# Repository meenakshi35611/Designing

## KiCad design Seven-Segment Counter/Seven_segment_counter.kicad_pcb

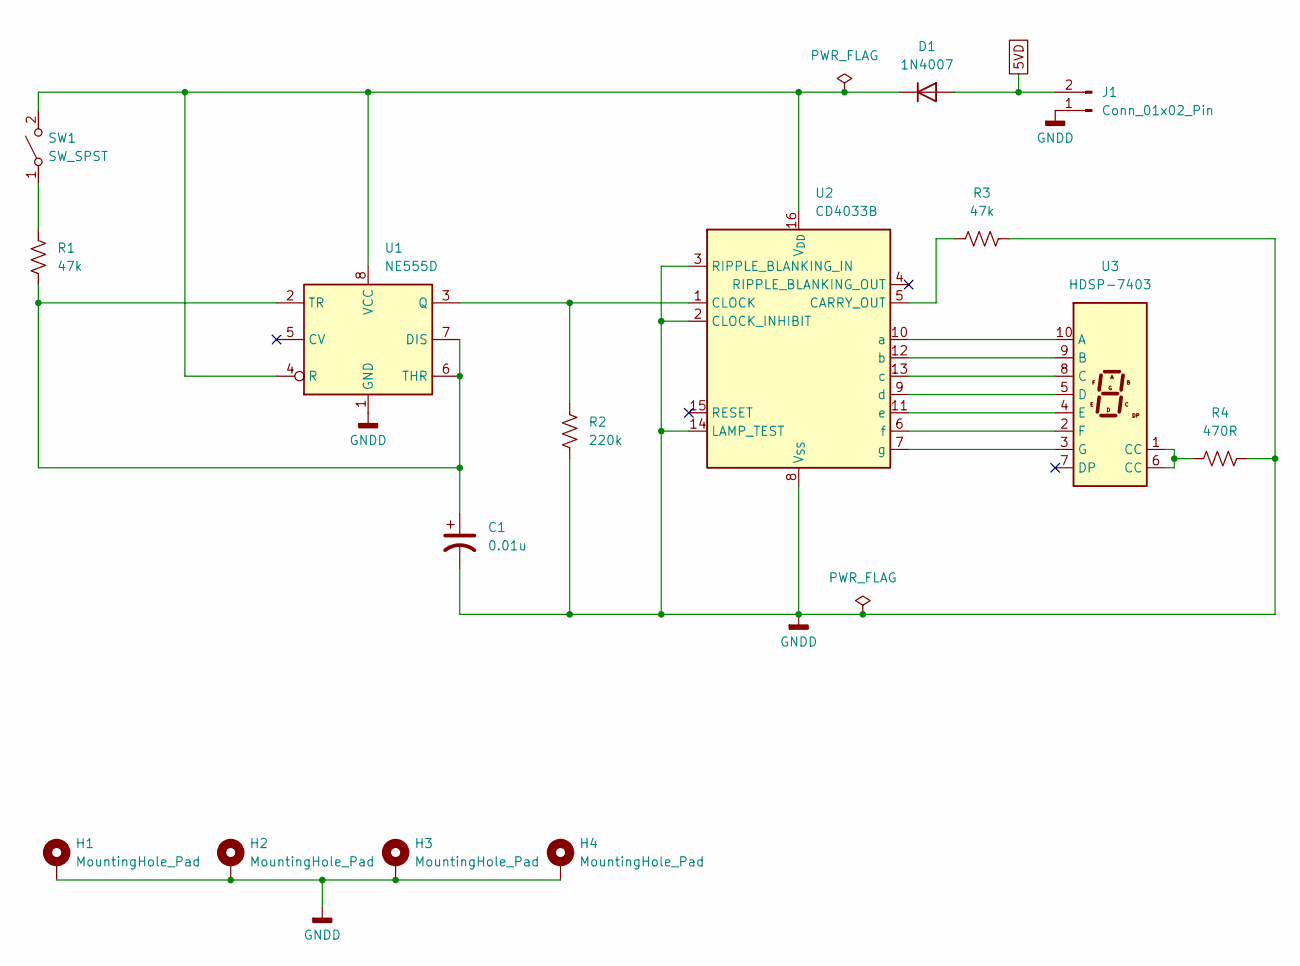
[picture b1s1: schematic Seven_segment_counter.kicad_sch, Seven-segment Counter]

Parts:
C1: 0.01u; C_0805_2012Metric
D1: 1N4007; D_DO-41_SOD81_P10.16mm_Horizontal
H1, H2, H3, H4: MountingHole_Pad; MountingHole_3.2mm_M3_Pad
J1: Conn_01x02_Pin; PinHeader_1x02_P2.54mm_Vertical
R1, R3: 47k; R_0805_2012Metric
R2: 220k; R_0805_2012Metric
R4: 470R; R_1206_3216Metric
SW1: SW_SPST; SW_DIP_SPSTx01_Slide_9.78x4.72mm_W7.62mm_P2.54mm
U1: NE555D; SOIC-8_3.9x4.9mm_P1.27mm
U2: CD4033B; DIP-16_W7.62mm
U3: HDSP-7403; HDSP-7401

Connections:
5VD: D1.2 (A), J1.2
GNDD: C1.2, H1.1, H2.1, H3.1, H4.1, J1.1, R2.2, R3.2, R4.1, U1.1 (GND), U2.2 (CLOCK_INHIBIT), U2.3 (RIPPLE_BLANKING_IN), U2.8 (V_{SS}), U2.14 (LAMP_TEST)
unnamed: D1.1 (K), SW1.2 (B), U1.4 (R), U1.8 (VCC), U2.16 (V_{DD})
unnamed: R4.2, U3.1 (CC), U3.6 (CC)
unnamed: R1.1, SW1.1 (A)
unnamed: C1.1, R1.2, U1.2 (TR), U1.6 (THR), U1.7 (DIS)
unnamed: R2.1, U1.3 (Q), U2.1 (CLOCK)
unnamed: R3.1, U2.5 (CARRY_OUT)
unnamed: U2.10 (a), U3.10 (A)
unnamed: U2.12 (b), U3.9 (B)
unnamed: U2.13 (c), U3.8 (C)
unnamed: U2.9 (d), U3.5 (D)
unnamed: U2.11 (e), U3.4 (E)
unnamed: U2.6 (f), U3.2 (F)
unnamed: U2.7 (g), U3.3 (G)

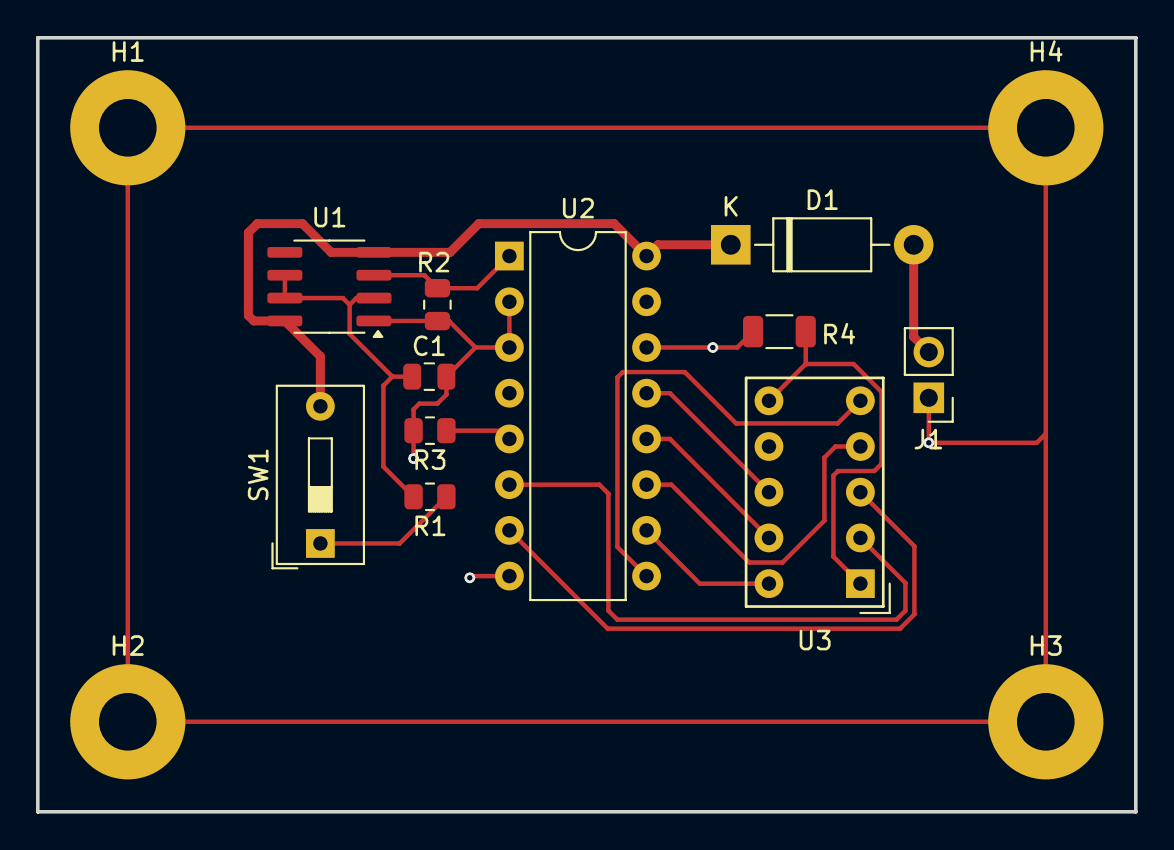
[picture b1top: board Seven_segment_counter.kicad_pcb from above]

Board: 2 copper layers, 61.0 x 43.0 mm, 15 parts (0 on the bottom side), 15 nets.

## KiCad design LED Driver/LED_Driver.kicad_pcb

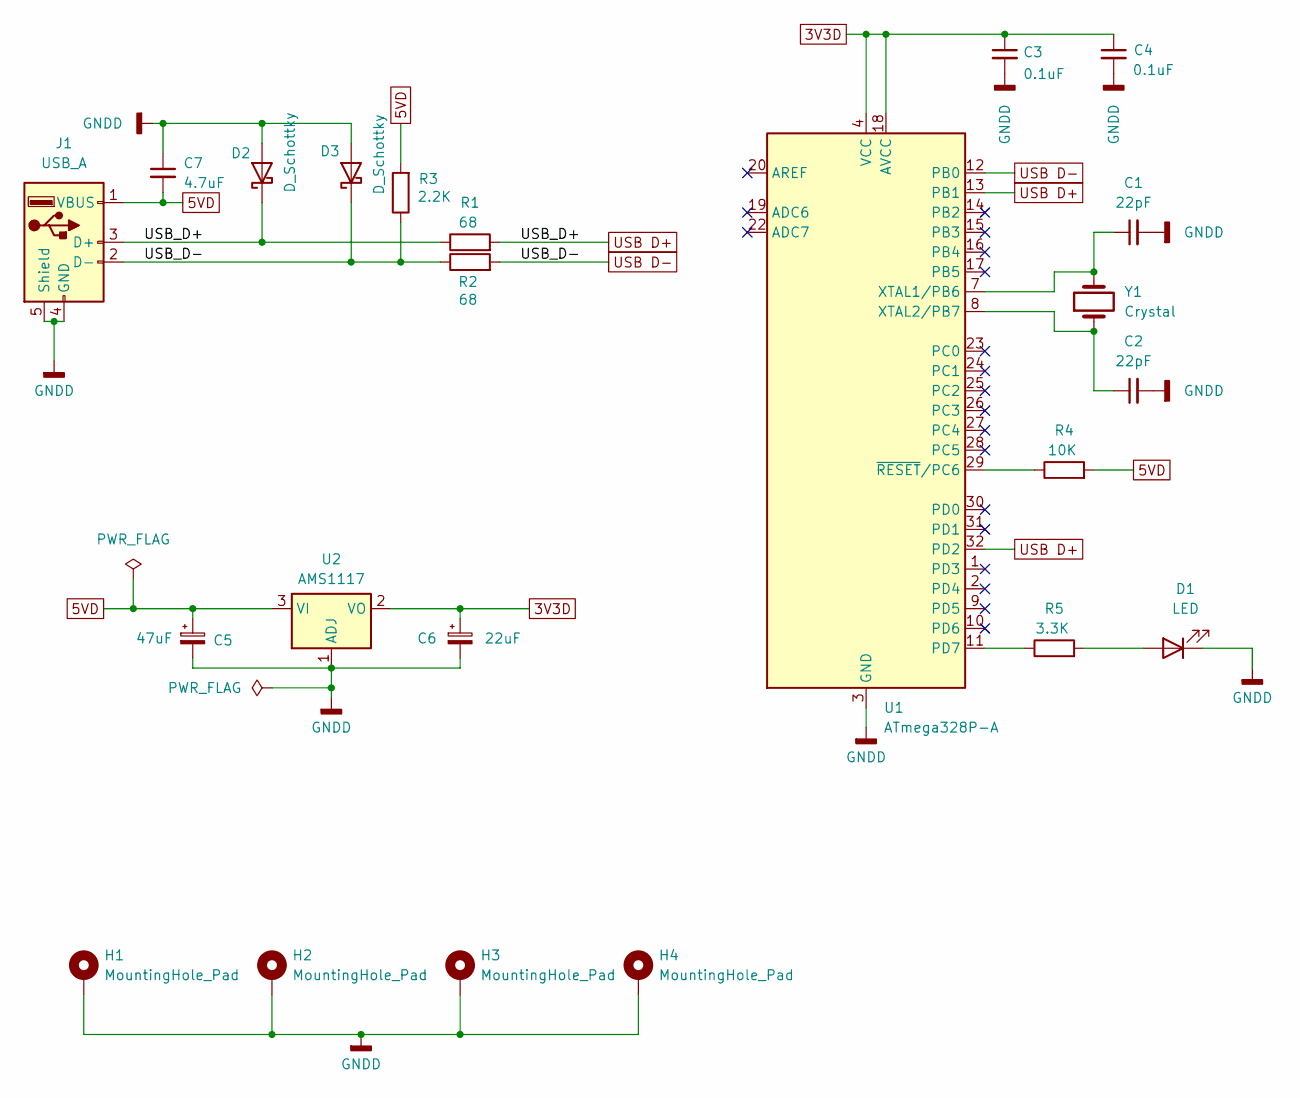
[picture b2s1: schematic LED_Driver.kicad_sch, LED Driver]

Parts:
C1, C2: 22pF; C_0805_2012Metric
C3, C4: 0.1uF; C_0805_2012Metric
C5: 47uF; C_1210_3225Metric
C6: 22uF; C_1210_3225Metric
C7: 4.7uF; C_1206_3216Metric
D1: LED; LED_D3.0mm
D2, D3: D_Schottky; D_SMA
H1, H2, H3, H4: MountingHole_Pad; MountingHole_3.2mm_M3_Pad
J1: USB_A; USB_A_Molex_67643_Horizontal
R1, R2: 68; R_0805_2012Metric
R3: 2.2K; R_0805_2012Metric
R4: 10K; R_0805_2012Metric
R5: 3.3K; R_0805_2012Metric
U1: ATmega328P-A; TQFP-32_7x7mm_P0.8mm
U2: AMS1117; SOT-223-3_TabPin2
Y1: Crystal; Crystal_SMD_HC49-SD

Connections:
3V3D: C3.1, C4.1, C6.1, U1.4 (VCC), U1.6 (VCC), U1.18 (AVCC), U2.2 (VO)
5VD: C5.1, C7.2, J1.1 (VBUS), R3.2, R4.2, U2.3 (VI)
GNDD: C1.2, C2.2, C3.2, C4.2, C5.2, C6.2, C7.1, D1.1 (K), D2.2 (A), D3.2 (A), H1.1, H2.1, H3.1, H4.1, J1.4 (GND), J1.5 (Shield), U1.3 (GND), U1.5 (GND), U1.21 (GND), U2.1 (ADJ)
unnamed: D1.2 (A), R5.2
unnamed: R5.1, U1.11 (PD7)
unnamed: C1.1, U1.7 (XTAL1/PB6), Y1.2
unnamed: C2.1, U1.8 (XTAL2/PB7), Y1.1
unnamed: R4.1, U1.29 (~RESET/PC6)
USB D+: D2.1 (K), J1.3 (D+), R1.1, R1.2, U1.13 (PB1), U1.32 (PD2)
USB D-: D3.1 (K), J1.2 (D-), R2.1, R2.2, R3.1, U1.12 (PB0)

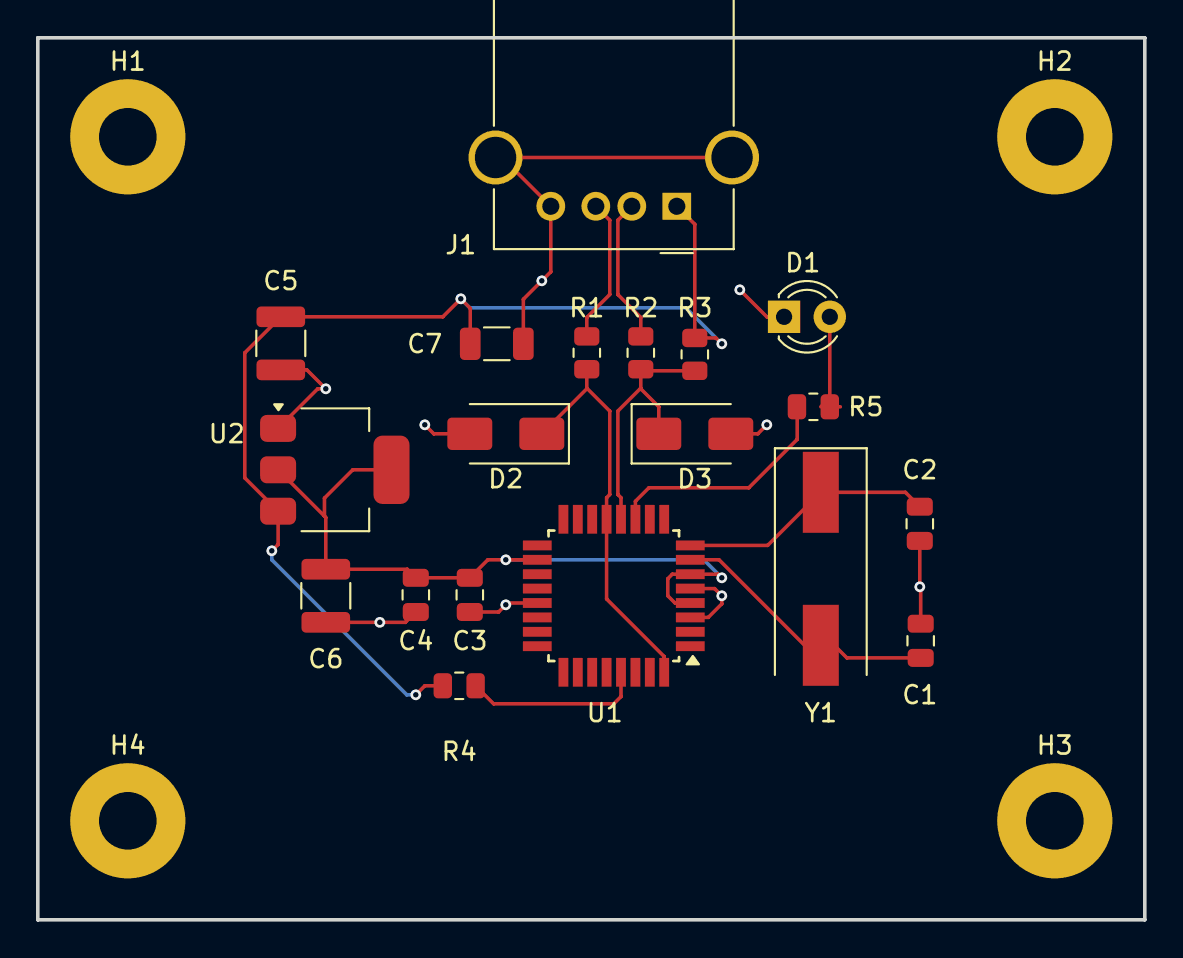
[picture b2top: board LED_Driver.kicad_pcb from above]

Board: 2 copper layers, 61.5 x 49.0 mm, 23 parts (0 on the bottom side), 10 nets.

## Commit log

2026-05-24 Create LED Driver
2026-05-24 Create Schematic
2026-05-24 Rename Screenshot 2026-05-24 124258.png to Schematic.png
2026-05-24 Rename Screenshot 2026-05-24 124343.png to Top_Layer.png
2026-05-24 Rename Screenshot 2026-05-24 124355.png to Bottom_Layer.png
2026-05-24 Create blah
2026-05-24 Rename Screenshot 2026-05-24 125230.png to Schematic.png
2026-05-24 Rename Screenshot 2026-05-24 130959.png to Top_Layer.png
2026-05-24 Rename Screenshot 2026-05-24 131009.png to Bottom_Layerpng
2026-05-24 Rename Bottom_Layerpng to Bottom_Layer.png
